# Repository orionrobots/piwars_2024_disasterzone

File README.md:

# piwars_2024_disasterzone

Code for Piwars 2024 robot

## 📋 Validation Infrastructure

See **[VALIDATION_ROADMAP.md](VALIDATION_ROADMAP.md)** for the plan to add offline validation (CI, testing, simulation).

## road map for motor board

Let's make the interface the same as the [GPIOzero Robot](https://gpiozero.readthedocs.io/en/stable/api_boards.html#robot). We can support this for multiple motor boards, and it will make it easier to swap them out.

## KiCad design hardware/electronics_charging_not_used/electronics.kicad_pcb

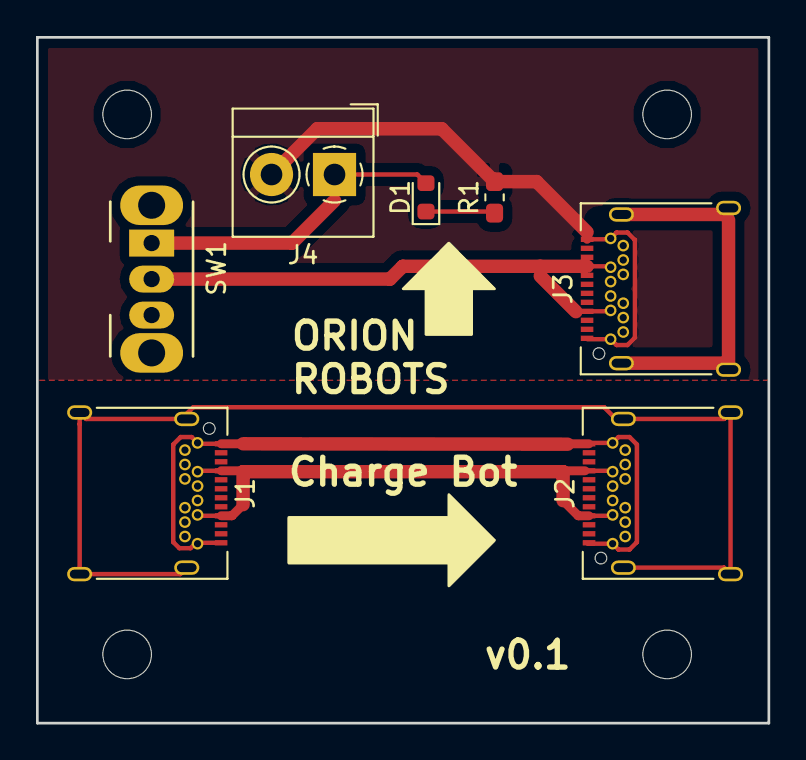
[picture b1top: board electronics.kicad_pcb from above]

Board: 2 copper layers, 40.6 x 38.1 mm, 7 parts (0 on the bottom side), 7 nets.

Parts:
D1: LED_Small; LED_0603_1608Metric
J1, J2, J3: USB_C_Receptacle_USB2.0; USB_C_Receptacle_Amphenol_12401548E4-2A
J4: Screw_Terminal_01x02; TerminalBlock_4Ucon_1x02_P3.50mm_Horizontal
R1: 330R; R_0603_1608Metric_Pad1.05x0.95mm_HandSolder
SW1: SW_SPDT; SW_CuK_OS102011MA1QN1_SPDT_Angled

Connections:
unnamed: D1.1, R1.1
unnamed: D1.2, J4.1, SW1.1
unnamed: J1.A1, J1.A12, J1.B1, J1.B12, J2.A1, J2.A12, J2.B1, J2.B12
unnamed: J1.A4, J1.A9, J1.B4, J1.B9, J2.A4, J2.A9, J2.B4, J2.B9
unnamed: J1.S1, J2.S1
unnamed: J3.A1, J3.A12, J3.B1, J3.B12, J4.2, R1.2
unnamed: J3.A4, J3.A9, J3.B4, J3.B9, SW1.2

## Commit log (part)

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2023-10-01 Starting code for lesson 2.
2023-10-08 additional setup
2023-10-15 Tidy this doc
2023-10-18 Whoops- didn't quite match the spec
2023-10-22 Rabbit?
2023-11-19 Add a settings system
2023-11-19 Missing file
2023-11-20 Moving board folders into services
2023-11-20 Update document - this looks like a win
2023-11-29 Bump cryptography from 41.0.4 to 41.0.6
    Bumps [cryptography](https://github.com/pyca/cryptography) from 41.0.4 to 41.0.6.
    - [Changelog](https://github.com/pyca/cryptography/blob/main/CHANGELOG.rst)
    - [Commits](https://github.com/pyca/cryptography/compare/41.0.4...41.0.6)
    ---
    updated-dependencies:
    - dependency-name: cryptography
2023-12-17 React app with joystick
2023-12-17 Create an installer for explorer hat pro service
2023-12-17 Deploy environment somewhere on the robot for services to pick up
2023-12-18 Document the content of this folder
2023-12-31 Fix silly swapped sped bug
2023-12-31 Install python paho as an apt package
2023-12-31 Not sure why, curve is backwards.
2024-01-08 Make use of common service parts
2024-01-11 Bump jinja2 from 3.1.2 to 3.1.3
    Bumps [jinja2](https://github.com/pallets/jinja) from 3.1.2 to 3.1.3.
    - [Release notes](https://github.com/pallets/jinja/releases)
    - [Changelog](https://github.com/pallets/jinja/blob/main/CHANGES.rst)
    - [Commits](https://github.com/pallets/jinja/compare/3.1.2...3.1.3)
    ---
    updated-dependencies:
2024-01-21 Re-enable system pip
2024-01-21 Handle the packages changed list properly.
2024-01-21 Yukon bugfixes: - Fix up logging messages - There's no monotonic - use time ticks. - We can't get motors until the modules are registered (maybe enabled) - JSon payload message errors should be logge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
2024-01-30 Bump paramiko from 2.12.0 to 3.4.0
    Bumps [paramiko](https://github.com/paramiko/paramiko) from 2.12.0 to 3.4.0.
    - [Commits](https://github.com/paramiko/paramiko/compare/2.12.0...3.4.0)
    ---
    updated-dependencies:
    - dependency-name: paramiko
    dependency-type: indirect
2024-02-11 Add the all stop handling. Better error handling.
2024-02-11 Tidy up electronics
2024-02-18 Bump expo from 49.0.21 to 50.0.7 in /robot_control
    Bumps [expo](https://github.com/expo/expo/tree/HEAD/packages/expo) from 49.0.21 to 50.0.7.
    - [Changelog](https://github.com/expo/expo/blob/main/packages/expo/CHANGELOG.md)
    - [Commits](https://github.com/expo/expo/commits/HEAD/packages/expo)
    ---
    updated-dependencies:
    - dependency-name: expo
2024-02-29 Bump expo from 49.0.21 to 50.0.8 in /robot_control
    Bumps [expo](https://github.com/expo/expo/tree/HEAD/packages/expo) from 49.0.21 to 50.0.8.
    - [Changelog](https://github.com/expo/expo/blob/main/packages/expo/CHANGELOG.md)
    - [Commits](https://github.com/expo/expo/commits/HEAD/packages/expo)
    ---
    updated-dependencies:
    - dependency-name: expo
2024-03-11 Stl shouldn't be here
2024-03-16 oops
2024-03-24 Pre-commit to improve the state of existing files
2024-03-25 Shoudln't be here
2024-03-26 Bump expo-updates from 0.18.19 to 0.24.12 in /orion_disaster_app
    Bumps [expo-updates](https://github.com/expo/expo/tree/HEAD/packages/expo-updates) from 0.18.19 to 0.24.12.
    - [Changelog](https://github.com/expo/expo/blob/main/packages/expo-updates/CHANGELOG.md)
    - [Commits](https://github.com/expo/expo/commits/HEAD/packages/expo-updates)
    ---
    updated-dependencies:
    - dependency-name: expo-updates
2024-04-07 LED's, buttons and coping with serial ports.
2024-04-14 Full nerf and grabber hardware
2024-04-16 Camera has a picture
2024-05-06 Bump jinja2 from 3.1.3 to 3.1.4
    Bumps [jinja2](https://github.com/pallets/jinja) from 3.1.3 to 3.1.4.
    - [Release notes](https://github.com/pallets/jinja/releases)
    - [Changelog](https://github.com/pallets/jinja/blob/main/CHANGES.rst)
    - [Commits](https://github.com/pallets/jinja/compare/3.1.3...3.1.4)
    ---
    updated-dependencies:
2024-05-17 Bump expo-updates from 0.18.19 to 0.25.14 in /orion_disaster_app
    Bumps [expo-updates](https://github.com/expo/expo/tree/HEAD/packages/expo-updates) from 0.18.19 to 0.25.14.
    - [Changelog](https://github.com/expo/expo/blob/main/packages/expo-updates/CHANGELOG.md)
    - [Commits](https://github.com/expo/expo/commits/HEAD/packages/expo-updates)
    ---
    updated-dependencies:
    - dependency-name: expo-updates
2024-06-05 Bump pydantic-settings from 2.3.0 to 2.3.1
    Bumps [pydantic-settings](https://github.com/pydantic/pydantic-settings) from 2.3.0 to 2.3.1.
    - [Release notes](https://github.com/pydantic/pydantic-settings/releases)
    - [Commits](https://github.com/pydantic/pydantic-settings/compare/v2.3.0...v2.3.1)
    ---
    updated-dependencies:
    - dependency-name: pydantic-settings
2024-06-17 Bump urllib3 from 2.1.0 to 2.2.2
    Bumps [urllib3](https://github.com/urllib3/urllib3) from 2.1.0 to 2.2.2.
    - [Release notes](https://github.com/urllib3/urllib3/releases)
    - [Changelog](https://github.com/urllib3/urllib3/blob/main/CHANGES.rst)
    - [Commits](https://github.com/urllib3/urllib3/compare/2.1.0...2.2.2)
    ---
    updated-dependencies:
2024-07-11 Bump @babel/core from 7.23.9 to 7.24.8 in /orion_disaster_app
    Bumps [@babel/core](https://github.com/babel/babel/tree/HEAD/packages/babel-core) from 7.23.9 to 7.24.8.
    - [Release notes](https://github.com/babel/babel/releases)
    - [Changelog](https://github.com/babel/babel/blob/main/CHANGELOG.md)
    - [Commits](https://github.com/babel/babel/commits/v7.24.8/packages/babel-core)
    ---
    updated-dependencies:
2024-07-22 Bump pyinfra from 2.9.2 to 3.0.1
    Bumps [pyinfra](https://github.com/Fizzadar/pyinfra) from 2.9.2 to 3.0.1.
    - [Release notes](https://github.com/Fizzadar/pyinfra/releases)
    - [Changelog](https://github.com/pyinfra-dev/pyinfra/blob/3.x/CHANGELOG.md)
    - [Commits](https://github.com/Fizzadar/pyinfra/compare/v2.9.2...v3.0.1)
    ---
    updated-dependencies:
2024-08-07 Bump expo-updates from 0.18.19 to 0.25.22 in /orion_disaster_app
    Bumps [expo-updates](https://github.com/expo/expo/tree/HEAD/packages/expo-updates) from 0.18.19 to 0.25.22.
    - [Changelog](https://github.com/expo/expo/blob/main/CHANGELOG.md)
    - [Commits](https://github.com/expo/expo/commits/HEAD/packages/expo-updates)
    ---
    updated-dependencies:
    - dependency-name: expo-updates
2024-09-10 Bump pydantic-settings from 2.3.4 to 2.5.0
    Bumps [pydantic-settings](https://github.com/pydantic/pydantic-settings) from 2.3.4 to 2.5.0.
    - [Release notes](https://github.com/pydantic/pydantic-settings/releases)
    - [Commits](https://github.com/pydantic/pydantic-settings/compare/v2.3.4...v2.5.0)
    ---
    updated-dependencies:
    - dependency-name: pydantic-settings
2024-09-25 Bump pyinfra from 3.1 to 3.1.1
    Bumps [pyinfra](https://github.com/Fizzadar/pyinfra) from 3.1 to 3.1.1.
    - [Release notes](https://github.com/Fizzadar/pyinfra/releases)
    - [Changelog](https://github.com/pyinfra-dev/pyinfra/blob/3.x/CHANGELOG.md)
    - [Commits](https://github.com/Fizzadar/pyinfra/compare/v3.1...v3.1.1)
    ---
    updated-dependencies:
2024-10-17 Bump pydantic-settings from 2.5.2 to 2.6.0
    Bumps [pydantic-settings](https://github.com/pydantic/pydantic-settings) from 2.5.2 to 2.6.0.
    - [Release notes](https://github.com/pydantic/pydantic-settings/releases)
    - [Commits](https://github.com/pydantic/pydantic-settings/compare/v2.5.2...v2.6.0)
    ---
    updated-dependencies:
    - dependency-name: pydantic-settings
2024-11-12 Bump expo-splash-screen from 0.20.5 to 0.29.7 in /orion_disaster_app
    Bumps [expo-splash-screen](https://github.com/expo/expo/tree/HEAD/packages/expo-splash-screen) from 0.20.5 to 0.29.7.
    - [Changelog](https://github.com/expo/expo/blob/main/packages/expo-splash-screen/CHANGELOG.md)
    - [Commits](https://github.com/expo/expo/commits/HEAD/packages/expo-splash-screen)
    ---
    updated-dependencies:
    - dependency-name: expo-splash-screen
2024-11-20 Bump expo-splash-screen from 0.20.5 to 0.29.12 in /orion_disaster_app
    Bumps [expo-splash-screen](https://github.com/expo/expo/tree/HEAD/packages/expo-splash-screen) from 0.20.5 to 0.29.12.
    - [Changelog](https://github.com/expo/expo/blob/main/packages/expo-splash-screen/CHANGELOG.md)
    - [Commits](https://github.com/expo/expo/commits/HEAD/packages/expo-splash-screen)
    ---
    updated-dependencies:
    - dependency-name: expo-splash-screen
2024-12-10 Bump expo-splash-screen from 0.20.5 to 0.29.18 in /orion_disaster_app
    Bumps [expo-splash-screen](https://github.com/expo/expo/tree/HEAD/packages/expo-splash-screen) from 0.20.5 to 0.29.18.
    - [Changelog](https://github.com/expo/expo/blob/main/CHANGELOG.md)
    - [Commits](https://github.com/expo/expo/commits/HEAD/packages/expo-splash-screen)
    ---
    updated-dependencies:
    - dependency-name: expo-splash-screen
2025-01-10 Bump expo-updates from 0.18.19 to 0.26.12 in /orion_disaster_app
    Bumps [expo-updates](https://github.com/expo/expo/tree/HEAD/packages/expo-updates) from 0.18.19 to 0.26.12.
    - [Changelog](https://github.com/expo/expo/blob/main/CHANGELOG.md)
    - [Commits](https://github.com/expo/expo/commits/HEAD/packages/expo-updates)
    ---
    updated-dependencies:
    - dependency-name: expo-updates
2025-05-20 Bump pydantic-settings from 2.5.2 to 2.7.1
    Bumps [pydantic-settings](https://github.com/pydantic/pydantic-settings) from 2.5.2 to 2.7.1.
    - [Release notes](https://github.com/pydantic/pydantic-settings/releases)
    - [Commits](https://github.com/pydantic/pydantic-settings/compare/v2.5.2...v2.7.1)
    ---
    updated-dependencies:
    - dependency-name: pydantic-settings
2025-05-20 Bump expo-splash-screen from 0.20.5 to 0.30.8 in /orion_disaster_app
    Bumps [expo-splash-screen](https://github.com/expo/expo/tree/HEAD/packages/expo-splash-screen) from 0.20.5 to 0.30.8.
    - [Changelog](https://github.com/expo/expo/blob/main/packages/expo-splash-screen/CHANGELOG.md)
    - [Commits](https://github.com/expo/expo/commits/HEAD/packages/expo-splash-screen)
    ---
    updated-dependencies:
    - dependency-name: expo-splash-screen
2025-06-05 Bump expo-updates from 0.18.19 to 0.28.14 in /orion_disaster_app
    Bumps [expo-updates](https://github.com/expo/expo/tree/HEAD/packages/expo-updates) from 0.18.19 to 0.28.14.
    - [Changelog](https://github.com/expo/expo/blob/main/CHANGELOG.md)
    - [Commits](https://github.com/expo/expo/commits/HEAD/packages/expo-updates)
    ---
    updated-dependencies:
    - dependency-name: expo-updates
2025-07-03 Bump expo-updates from 0.18.19 to 0.28.16 in /orion_disaster_app
    Bumps [expo-updates](https://github.com/expo/expo/tree/HEAD/packages/expo-updates) from 0.18.19 to 0.28.16.
    - [Changelog](https://github.com/expo/expo/blob/main/CHANGELOG.md)
    - [Commits](https://github.com/expo/expo/commits/HEAD/packages/expo-updates)
    ---
    updated-dependencies:
    - dependency-name: expo-updates
2025-07-22 Bump form-data from 3.0.1 to 3.0.4 in /orion_disaster_app
    Bumps [form-data](https://github.com/form-data/form-data) from 3.0.1 to 3.0.4.
    - [Release notes](https://github.com/form-data/form-data/releases)
    - [Changelog](https://github.com/form-data/form-data/blob/v3.0.4/CHANGELOG.md)
    - [Commits](https://github.com/form-data/form-data/compare/v3.0.1...v3.0.4)
    ---
    updated-dependencies:
2025-09-10 Bump expo-updates from 0.18.19 to 29.0.9 in /orion_disaster_app
    Bumps [expo-updates](https://github.com/expo/expo/tree/HEAD/packages/expo-updates) from 0.18.19 to 29.0.9.
    - [Changelog](https://github.com/expo/expo/blob/main/packages/expo-updates/CHANGELOG.md)
    - [Commits](https://github.com/expo/expo/commits/HEAD/packages/expo-updates)
    ---
    updated-dependencies:
    - dependency-name: expo-updates
2025-10-01 Bump expo-updates from 0.18.19 to 29.0.12 in /orion_disaster_app
    Bumps [expo-updates](https://github.com/expo/expo/tree/HEAD/packages/expo-updates) from 0.18.19 to 29.0.12.
    - [Changelog](https://github.com/expo/expo/blob/main/CHANGELOG.md)
    - [Commits](https://github.com/expo/expo/commits/HEAD/packages/expo-updates)
    ---
    updated-dependencies:
    - dependency-name: expo-updates
